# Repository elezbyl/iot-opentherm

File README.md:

# IoT OpenTherm Project

Project here called **IoT OpenTherm** is IoT device project to control the furnace using OpenTherm protocol/interface. This device allows to integrate OpenTherm compatible endpoint/slave with IoT infrastructure. Project is inspired with following projects:
* https://ihormelnyk.com/opentherm_thermostat
* https://olegtarasov.me/opentherm-thermostat-esphome
* https://github.com/arthurrump/esphome-opentherm

Repository here contains multiple components like HW, FW, SW, docs.

To clone the repository:
```
git clone --recurse-submodules https://github.com/elezbyl/iot-opentherm.git
```

## HW
IoT OpenTherm HW Project is based on ESP-12S WiFi module and Ihor's Melnyk adapter design. More details can be found [here](hw/README.md)

## FW
There are various different IoT FW stack which could be used for IoT OpenTherm project. More details can be found [here](fw/README.md)

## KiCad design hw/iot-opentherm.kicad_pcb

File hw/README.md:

# IoT OpenTherm Project Hardware
IoT OpenTherm Hardware project is based on ESP-12S wifi module (used ESP8266 chip) and analog circuit derived from Ihor Melnyk [OpenTherm Adapter](https://ihormelnyk.com/opentherm_adapter) design.

## EDA
Project is prepared with KiCAD

### Version
Version: 8.0.5, release build

Libraries:
* wxWidgets 3.2.5
* FreeType 2.13.2
* HarfBuzz 9.0.0
* FontConfig 2.14.2
* libcurl/8.8.0-DEV Schannel zlib/1.3.1

Build Info:
* Date: Sep 7 2024 02:39:48
* wxWidgets: 3.2.5 (wchar_t,wx containers)
* Boost: 1.85.0
* OCC: 7.8.1
* Curl: 8.8.0-DEV
* ngspice: 42
* Compiler: Visual C++ 1939 without C++ ABI

## Components

* AiThinker ESP-12S WiFi module based on ESP8266 SoC. Documentation:
   * [ESP8266EX Datasheet](https://www.espressif.com/sites/default/files/documentation/0a-esp8266ex_datasheet_en.pdf)
   * [ESP8266 Technical Reference](https://www.espressif.com/sites/default/files/documentation/esp8266-technical_reference_en.pdf)
   * [ESP-12S Product Specification](../doc/ESP-12S%20-%20Product%20Specification.pdf)
   * [ESP-12S Specification](../doc/ESP-12S%20-%20Specification.pdf)
   * [ESP-12S Datasheet](../doc/ESP-12S%20-%20Datasheet.pdf)
   * [ESP-12S User Manual](../doc/ESP-12S%20-%20User%20Manual.pdf)
   * [ESP-12S Pinout](https://tasmota.github.io/docs/Pinouts/#esp-12s)
* Molex 475900001 USB AB micro connector: [details](https://www.molex.com/en-us/products/part-detail/475900001)
* 1117-3.3 (3.3V/1A) LDO, SOT-223: [details](https://www.st.com/resource/en/datasheet/ld1117.pdf)
* BC858 (A/B/C) PNP Transistor, SOT-23
* PC817 Photocoupler, SO-4
* Resistors 0603
* Capacitors 0603 and 0805
* Diodes (switching and Zeners) SOD-323
* Headers 2.54mm

### BOM
BOM can be found [here](bom.csv)

## PCB

### Vendor
[JLCPCB](https://jlcpcb.com)

### Stackup
* Material: FR4-Standard TG 135-140
* Layers count: 4 (L1.Signal, L2.GND, L3.VCC, L4.Signal)
* PCB Thickness: 1.6mm
* Prepreg: TBD
* PCB stackup: TBD 
* Via hole:
  * 12mils (0.3mm) for signals
  * 15mils (0.38mm) for power 1
  * 20mils (0.5mm) for power 2
* Via diameter:
  * 30mils (0.64mm) for signals
  * 35mils (0.89mm) for power 1
  * 45mils (1.00mm) for power 2
* Via annular ring:
  * 9mils (0.23mm) for signal
  * 10mils (0.25mm) for power 1
  * 15mils (0.38mm) for power 2
* Silkscreen: 30mils x 30mils x 6mils

More details about JLCPCB capabilities can be found [here](https://jlcpcb.com/capabilities/pcb-capabilities)

## Design
### Version 1.00
[SCH](doc/iot-opentherm_sch_v1p00.pdf)

[PCB](doc/iot-opentherm_pcb_v1p00.pdf)

[GERBERS](gerbers/gerbers_v1p00.zip)

BOARD:

### Version 1.01
:construction:
Under construction
:construction:

Changes in comparison to the v1.00:
* changed footprints for D1/D2/D3/D4 to bigger one
* added connectors for OTx and +5VDC
* GPIOs for OT communication swapped to be aligned with Ihor's Melnyk adapter design and Arthur Rump FW solution
* added labels for OTx and +5VDC

## Tests
There are two types of test done. First, static test, with no OpenTherm endpoint device. Second, with OpenTherm endpoint device connected - boiler.

**Test was done for HW version 1.00**

### Static tests
Test was done by static voltage and current values verification at different parts of the circuit at different cases. It was done with no OpenTherm compatible endpoint connected.

Measurements were done for two different voltage values (4V, 15V) and four different current values (5mA, 9mA, 17mA, 23mA) at OT connector/pins. Those conditions (voltage and current) were inducted with power supply connected to OT connector/pins. For all test cases/points - power supply were configured to deliver 20V and different maximum current values ( 5mA, 9mA, 17mA, 23mA). Voltage at OT was clamped to ~15V when IN=LOW and to ~4V when IN=HIGH, which is expected. It proves that communication from controller (wifi module) to endpoint (boiler) works fine. Maximum current value were configured in power supplier for four different points: 5mA, 9mA, 17mA, 23mA. Those points were chosen as they are limit values specified in the [The OpenTherm Communications Protocol Specification](https://ihormelnyk.com/Content/Pages/opentherm_library/Opentherm%20Protocol%20v2-2.pdf).

Requirements:
* when IN=LOW, OT voltage >= 15V
* when IN=HIGH, OT voltage <= 7V
* when OT current is <=9mA, OUT < 0.8V
* when OT current is >=17mA, OUT > 2.0V

Below there are test results.

Test Points

Measurements at Test Points for different voltage and current values at OT connector/pins
| OT Voltage [V] | OT Current [mA] | TP1 [V] | TP2 [V] | TP3 [V] | TP4 [V] | TP5 [V] | TP6/OUT [V] |
| -------------- | --------------- | ------- | ------- | ------- | ------- | ------- | ----------- |
| 15 (IN=LOW)    | 5               | 15.75   | 15.12   | 0.95    | 0.27    | 0       | 0           |
| 15 (IN=LOW)    | 9               | 15.78   | 15.06   | 2.44    | 0.72    | 0       | 0           |
| 15 (IN=LOW)    | 17              | 15.81   | 15.12   | 4.37    | 1.13    | 0       | 3.11        |
| 15 (IN=LOW)    | 23              | 15.83   | 15.11   | 4.64    | 1.14    | 0       | 3.12        |
| 4 (IN=HIGH)    | 5               | 4.76    | 4.12    | 0.91    | 0.26    | 4.12    | 0           |
| 4 (IN=HIGH)    | 9               | 4.81    | 4.14    | 2.44    | 0.70    | 4.01    | 0           |
| 4 (IN=HIGH)    | 17              | 4.86    | 4.16    | 4.33    | 1.13    | 4.03    | 3.10        |
| 4 (IN=HIGH)    | 23              | 4.89    | 4.18    | 4.63    | 1.14    | 4.03    | 3.11        |

Conclusions:
* all the requirements were satisfied
* the only concern is about the voltage at IN which was 3.1V in HIGH. Expected more. This does not impact functionality of the circuit. But it will be investigated anyway.

### Tests with OpenTherm compatible endpoint, e.g. boiler.
TBD

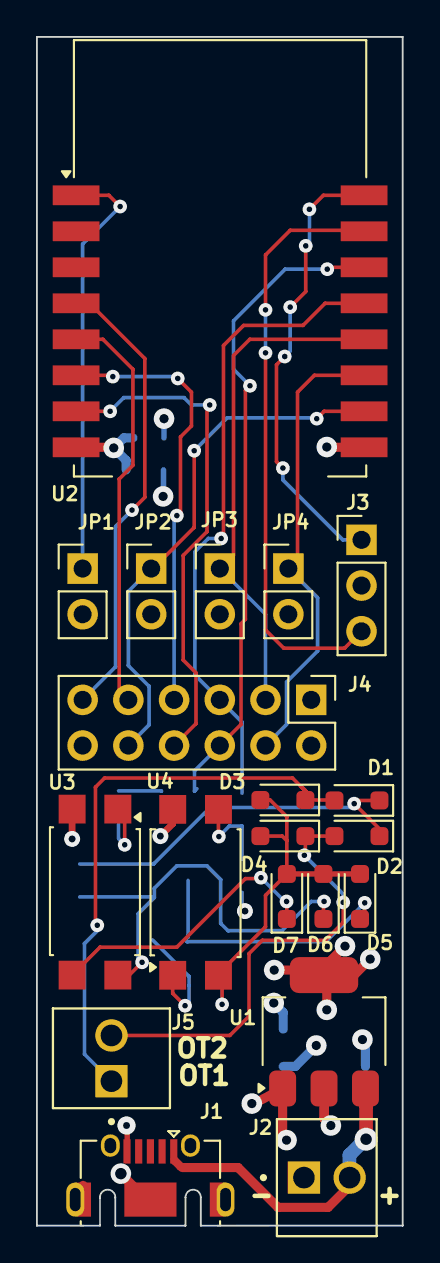
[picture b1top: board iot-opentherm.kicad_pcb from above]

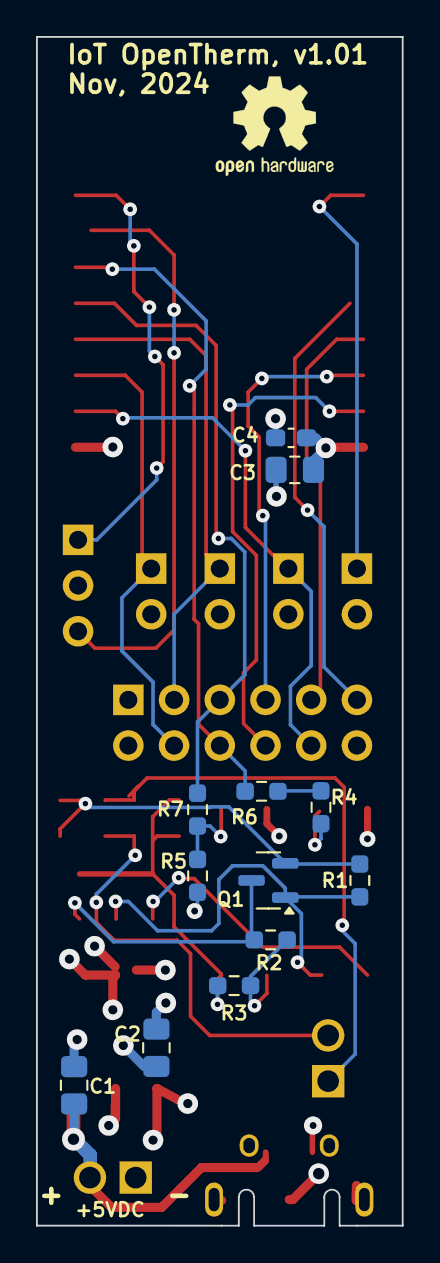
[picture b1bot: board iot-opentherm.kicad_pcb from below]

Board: 4 copper layers, 20.3 x 66.0 mm, 32 parts (12 on the bottom side), 26 nets.

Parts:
C1, C2: 22u; C_0805_2012Metric_Pad1.18x1.45mm_HandSolder
C3: 10u; C_0805_2012Metric_Pad1.18x1.45mm_HandSolder
C4: 100n; C_0603_1608Metric_Pad1.08x0.95mm_HandSolder
D1, D2, D3, D4: 1N4148WS; D_SOD-323_HandSoldering
D5: 4V7; D_SOD-323_HandSoldering
D6: 15V; D_SOD-323_HandSoldering
D7: 4V3; D_SOD-323_HandSoldering
J1: USB_B_Micro; USB_Micro-AB_Molex_47590-0001
J2, J5: Conn_01x02; TE_282834-2
J3: Conn_01x03; PinHeader_1x03_P2.54mm_Vertical
J4: Conn_02x06_Odd_Even; PinHeader_2x06_P2.54mm_Vertical
JP1, JP2, JP3, JP4: Jumper_2_Open; PinHeader_1x02_P2.54mm_Vertical
Q1: BC858; SOT-23
R1, R4: 330R; R_0603_1608Metric_Pad0.98x0.95mm_HandSolder
R2: 220R; R_0603_1608Metric_Pad0.98x0.95mm_HandSolder
R3: 100R; R_0603_1608Metric_Pad0.98x0.95mm_HandSolder
R5: 1.5k; R_0603_1608Metric_Pad0.98x0.95mm_HandSolder
R6, R7: 33R; R_0603_1608Metric_Pad0.98x0.95mm_HandSolder
U1: AMS1117-3.3; SOT-223-3_TabPin2
U2: ESP-12S
U3, U4: PC817; SO-4_6.5x4.6mm_P2.54mm

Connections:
+3.3V: C2.1, C3.1, C4.1, J4.1, JP2.2 (B), U1.2 (VO), U2.8 (VCC), U4.4
+5V: C1.1, J1.1 (VBUS), J2.2, U1.3 (VI)
/GPIO0: J4.3, JP3.1 (A), U2.12 (GPIO0)
/GPIO1_TXD: J3.1, U2.16 (GPIO1/TXD)
/GPIO2: J4.4, JP4.1 (A), U2.11 (GPIO2)
/GPIO3_RXD: J3.3, U2.15 (GPIO3/RXD)
/GPIO4: J4.5, R7.1, U2.13 (GPIO4)
/GPIO5: J4.6, R6.1, U2.14 (GPIO5)
/GPIO12: J4.7, U2.6 (GPIO12)
/GPIO13: J4.8, U2.7 (GPIO13)
/GPIO14: J4.9, U2.5 (GPIO14)
/GPIO15: J4.10, JP2.1 (A), U2.10 (GPIO15)
/GPIO16: J4.11, U2.4 (GPIO16)
/IN: R4.2, R6.2
/OT1: D1.2 (A), D3.1 (K), J5.1
/OT2: D2.2 (A), D4.1 (K), J5.2
/OUT: R5.1, R7.2, U4.3
GND: C1.2, C2.2, C3.2, C4.2, J1.5 (GND), J1.6 (Shield), J2.1, J3.2, J4.2, J4.12, JP1.2 (B), JP3.2 (B), JP4.2 (B), R5.2, U1.1 (GND), U2.9 (GND), U3.2
unnamed: D1.1 (K), D2.1 (K), Q1.2 (E), R1.1
unnamed: D3.2 (A), D4.2 (A), D5.2 (A), D6.2 (A), D7.2 (A), R3.2, U4.2
unnamed: D5.1 (K), Q1.3 (C), R2.1
unnamed: D6.1 (K), Q1.1 (B), R1.2, U3.4
unnamed: D7.1 (K), U3.3
unnamed: JP1.1 (A), U2.1 (~RST)
unnamed: R2.2, R3.1, U4.1
unnamed: R4.1, U3.1

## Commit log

2024-11-07 Initial version
    Added docs with some documents regarding HW
    Added README files
    Added initial HW project version (1.00)
    Added BOM
    Added Gerbers
    Added ERC and DRC reports
2024-11-07 Fixes after running first version
    1. Corrected footprint for D1, D2, D3, D4 to bigger one
    2. Added connectors for OTx and +5VDC.
    3. Added labels for OTx and +5VDC
    4. ERC: no regression
    5. DRC: two more issues
2024-11-07 Fixes after running first version
    1. Corrected footprint for D1, D2, D3, D4 to bigger one
    2. Added connectors for OTx and +5VDC.
    3. GPIOs for OT communication swapped to be aligned with Ihor's Melnyk
    adapter design and Arthur Rump FW solution
    4. Added labels for OTx and +5VDC
    5. ERC: no regression
2024-11-20 Some cleanup
    1. Added picture of the board in main README file.
    2. Added OSHW logo in main README file.
    3. Updated repo cloning procedure.
2024-11-20 Some cleanup (#2)
    1. Added picture of the board in main README file.
    2. Added OSHW logo in main README file.
    3. Updated repo cloning procedure.
